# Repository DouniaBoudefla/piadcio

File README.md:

PIADC-IO

PIADC-IO is a versatile and I/O expansion project designed to enhance the GPIO capabilities of the Raspberry Pi. The project integrates the MCP23S08 I/O expander and the MCP3208 ADC (Analog-to-Digital Converter) with the Raspberry Pi, enabling efficient control of multiple devices and precise analog signal measurements via the SPI protocol. This repository contains all the necessary resources, including schematics, PCB designs, code, and documentation, to set up and use the PIADC-IO system for various applications, such as slow control in experimental setups and monitoring analog inputs.

Features

I/O Expansion: Utilize the MCP23S08 to expand the Raspberry Pi's GPIO capabilities by 8 configurable pins per expander, supporting multiple input/output configurations.
Analog-to-Digital Conversion: Integrate the MCP3208 to enable reading from up to 8 analog input channels with 12-bit resolution.
Power Indication LED: Monitor power status with a controllable LED, which can be managed via the Raspberry Pi.
Modular and Configurable: Easily adapt the system to different hardware setups with a TOML configuration file used to define hardware-specific settings like SPI bus numbers and chip select lines.

Repository Structure

pcb/ - Includes PCB design files and contains the electronic schematics used for the project, designed in KiCad.
src/ - Source code for interacting with the MCP23S08 and MCP3208, including Python classes for each.

Preliminary Configuration

Before starting, you need to enable the SPI function on your Raspberry Pi using 'raspi-config'.
The Raspberry Pi have 2 different SPI bus: one will be known as /dev/spi0.* and the other as /dev/spi1.*.

Enabling SPI1

if '/dev/spi1.0' and '/dev/spi1.1' are not available, you need to enable SPI1 manually:

1. Edit the boot configuration file:

        sudo nano /boot/config.txt

2. Add the following lines at the end of the file to enable SPI1:

        dtparam=spi=on
        dtoverlay=spi1-3cs

3. Save the file and exit the editor (Ctrl + O, Enter, Ctrl + X)
4. Reboot your Raspberry Pi to apply the changes:

        sudo reboot

After rebooting, you should see '/dev/spi1.0' and '/dev/spi1.1' available for use.

Communication with MCP23S08

To communicate with MCP23S08, you need to send and receive data via the SPI interface. Here is how you can read from and write to the the MCP23S08 registers using Python with the 'spidev' library.

Understanding MCP23S08 Communication

Commmand Structure

Communication with the MCP23S08 involves sending a sequence of bytes over the SPI interface. 
Each command generally consists of the following parts:

- Opcode: Determines whether the operation is a read or write
- Register Address: Specifies which register to access
- Data: The value to write to the register (for write operations)

Opcode

Write Opcode: Ox40 (A0=0, A1=0)
Read Opcode: 0x41 (A0=0, A1=0)

The opcode is followed by the register address and then the data byte

Register Address

The MCP23S08 has several registers for configuring and controlling the I/Os. Here are some key registers:

- IODIR (0X00): I/O Direction Register (1 = input, 0 = output)
- GPIO (0x09): GPIO Register (read/write I/O values)
- OLAT (0x0A): Output Latch Register (maintain output values)

Data 

The data byte is the value you write to the register. For read operations, the data byte received from the MCP23S08 will contain the registers's current value.

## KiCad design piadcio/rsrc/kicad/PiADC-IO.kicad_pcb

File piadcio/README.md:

PIADC-IO

PIADC-IO is a versatile and I/O expansion project designed to enhance the GPIO capabilities of the Raspberry Pi. The project integrates the MCP23S08 I/O expander and the MCP3208 ADC (Analog-to-Digital Converter) with the Raspberry Pi, enabling efficient control of multiple devices and precise analog signal measurements via the SPI protocol. This repository contains all the necessary resources, including schematics, PCB designs, code, and documentation, to set up and use the PIADC-IO system for various applications, such as slow control in experimental setups and monitoring analog inputs.

Features

I/O Expansion: Utilize the MCP23S08 to expand the Raspberry Pi's GPIO capabilities by 8 configurable pins per expander, supporting multiple input/output configurations.
Analog-to-Digital Conversion: Integrate the MCP3208 to enable reading from up to 8 analog input channels with 12-bit resolution.
Power Indication LED: Monitor power status with a controllable LED, which can be managed via the Raspberry Pi.
Modular and Configurable: Easily adapt the system to different hardware setups with a TOML configuration file used to define hardware-specific settings like SPI bus numbers and chip select lines.

Repository Structure

pcb/ - Includes PCB design files and contains the electronic schematics used for the project, designed in KiCad.
src/ - Source code for interacting with the MCP23S08 and MCP3208, including Python classes for each.

Preliminary Configuration

Before starting, you need to enable the SPI function on your Raspberry Pi using 'raspi-config'.
The Raspberry Pi have 2 different SPI bus: one will be known as /dev/spi0.* and the other as /dev/spi1.*.

Enabling SPI1

    if '/dev/spi1.0' and '/dev/spi1.1' are not available, you need to enable SPI1 manually:

    1. Edit the boot configuration file:

        sudo nano /boot/config.txt

    2. Add the following lines at the end of the file to enable SPI1:

        dtparam=spi=on
        dtoverlay=spi1-3cs

    3. Save the file and exit the editor (Ctrl + O, Enter, Ctrl + X)
    4. Reboot your Raspberry Pi to apply the changes:

        sudo reboot

    After rebooting, you should see '/dev/spi1.0' and '/dev/spi1.1' available for use.

Communication with MCP23S08

To communicate with MCP23S08, you need to send and receive data via the SPI interface. Here is how you can read from and write to the the MCP23S08 registers using Python with the 'spidev' library.

Understanding MCP23S08 Communication

Commmand Structure

Communication with the MCP23S08 involves sending a sequence of bytes over the SPI interface. 
Each command generally consists of the following parts:

- Opcode: Determines whether the operation is a read or write
- Register Address: Specifies which register to access
- Data: The value to write to the register (for write operations)

Opcode

Write Opcode: Ox40 (A0=0, A1=0)
Read Opcode: 0x41 (A0=0, A1=0)

The opcode is followed by the register address and then the data byte

Register Address

The MCP23S08 has several registers for configuring and controlling the I/Os. Here are some key registers:

- IODIR (0X00): I/O Direction Register (1 = input, 0 = output)
- GPIO (0x09): GPIO Register (read/write I/O values)
- OLAT (0x0A): Output Latch Register (maintain output values)

Data 

The data byte is the value you write to the register. For read operations, the data byte received from the MCP23S08 will contain the registers's current value.

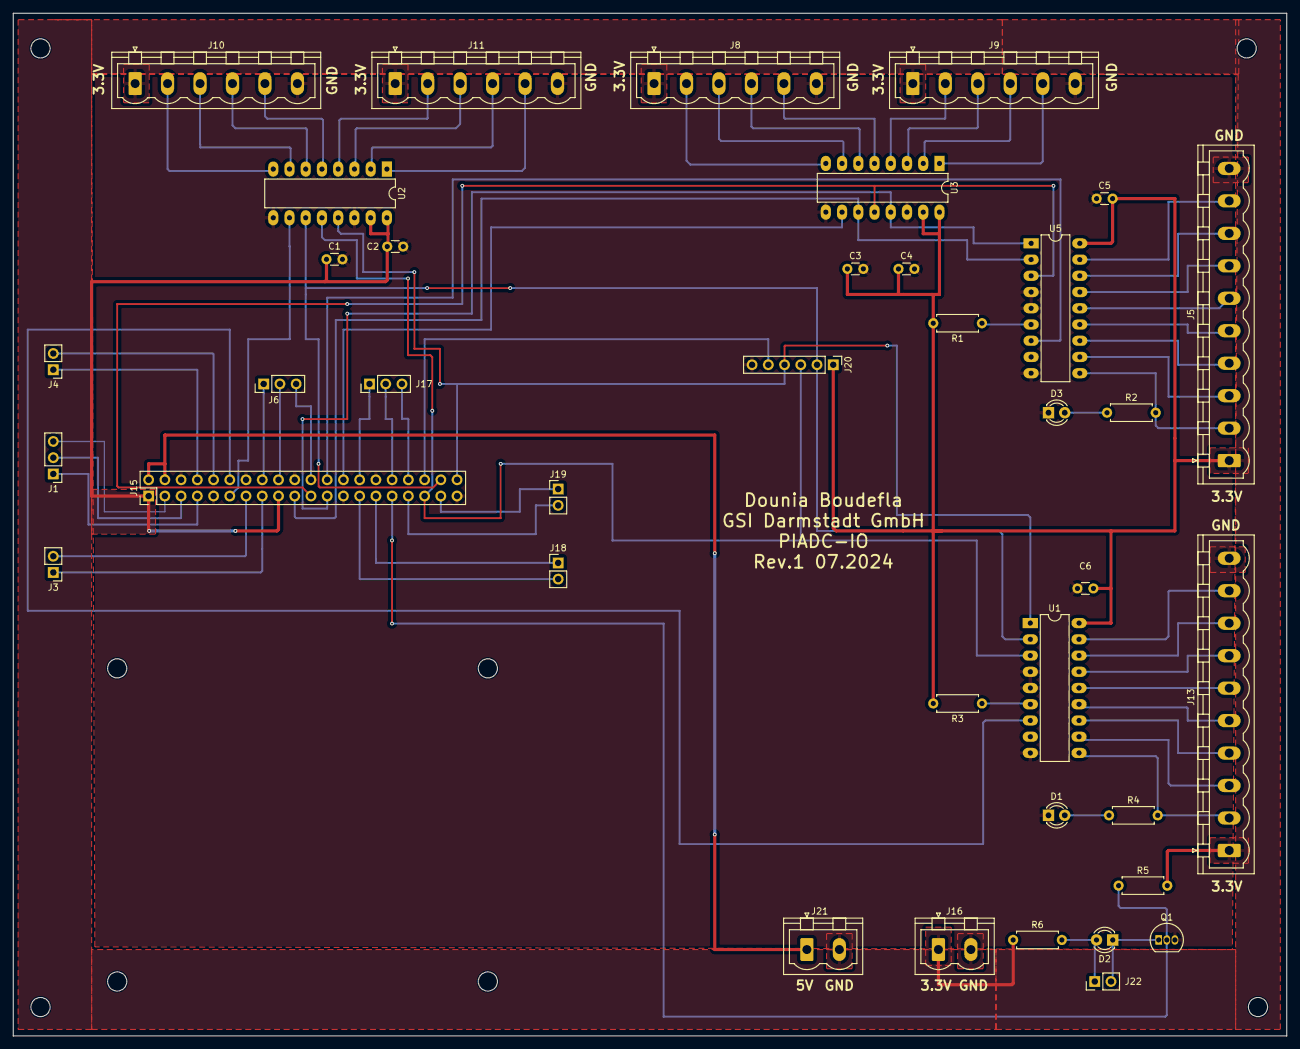
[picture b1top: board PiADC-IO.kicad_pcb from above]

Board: 2 copper layers, 199.3 x 160.0 mm, 43 parts (0 on the bottom side), 70 nets.

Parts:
C1, C3: 10nF; C_Disc_D3.0mm_W1.6mm_P2.50mm
C2, C4, C5, C6: 100nF; C_Disc_D3.0mm_W1.6mm_P2.50mm
D1, D2, D3: LED Red; LED_D3.0mm
H1, H2, H3, H4: MountingHole; MountingHole_3mm
J1, J6, J17: Conn_01x03; PinHeader_1x03_P2.54mm_Vertical
J2: Raspberry_Pi_2_3; raspberrypi_NOCONNECTOR
J3, J4, J18, J19, J22: Conn_01x02; PinHeader_1x02_P2.54mm_Vertical
J5, J13: Conn_01x10; PhoenixContact_MSTBVA_2,5_10-G-5,08_1x10_P5.08mm_Vertical
J8, J9, J10, J11: Conn_01x06; PhoenixContact_MSTBVA_2,5_6-G-5,08_1x06_P5.08mm_Vertical
J15: RPI conn; PinHeader_2x20_P2.54mm_Vertical
J16: Raspberry Pi USB Power; PhoenixContact_MSTBVA_2,5_2-G-5,08_1x02_P5.08mm_Vertical
J20: Conn_01x06; PinHeader_1x06_P2.54mm_Vertical
J21: 5V; PhoenixContact_MSTBVA_2,5_2-G-5,08_1x02_P5.08mm_Vertical
Q1: BS170; TO-92_Inline
R1, R3, R5: 4.7K; R_Axial_DIN0207_L6.3mm_D2.5mm_P7.62mm_Horizontal
R2, R4, R6: 470R; R_Axial_DIN0207_L6.3mm_D2.5mm_P7.62mm_Horizontal
U1, U5: MCP23S08-I/O Expander; DIP-18_W7.62mm_LongPads
U2, U3: MCP3208-ADC; DIP-16_W7.62mm_LongPads

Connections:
+3.3V: C1.1, C2.1, C3.1, C4.1, C5.2, C6.2, J5.1, J8.1, J9.1, J10.1, J11.1, J13.1, J15.1, J15.17, J16.1, J20.1, R1.2, R3.2, R5.2, R6.1, U1.18 (VDD), U2.15 (Vref), U2.16 (Vdd), U3.15 (Vref), U3.16 (Vdd), U5.18 (VDD)
+5V: J15.2, J15.4, J21.1
/CS 0_0: J15.24, U5.7 (~CS)
/CS 0_1: J15.26, U3.10 (~CS/SHDN)
/CS 1_0: J15.12, U1.7 (~CS)
/CS 1_1: J15.11, U2.10 (~CS/SHDN)
/CS 1_2: J15.36, J20.5
/MISO 0: J15.21, U3.12 (Dout), U5.3 (SO)
/MISO 1: J15.35, J20.3, U1.3 (SO), U2.12 (Dout)
/MOSI 0: J15.19, U3.11 (Din), U5.2 (SI)
/MOSI 1: J15.38, J20.2, U1.2 (SI), U2.11 (Din)
/SCLK 0: J15.23, U3.13 (CLK), U5.1 (SCK)
/SCLK 1: J15.40, J20.4, U1.1 (SCK), U2.13 (CLK)
GND: C1.2, C2.2, C3.2, C4.2, C5.1, C6.1, D1.1 (K), D3.1 (K), J5.10, J8.6, J9.6, J10.6, J11.6, J13.10, J15.6, J15.9, J15.14, J15.20, J15.25, J15.30, J15.39, J16.2, J20.6, J21.2, Q1.3 (S), U1.4 (A1), U1.5 (A0), U1.9 (VSS), U2.9 (DGND), U2.14 (AGND), U3.9 (DGND), U3.14 (AGND), U5.4 (A1), U5.5 (A0), U5.9 (VSS)
unnamed: D1.2 (A), R4.1
unnamed: D2.2 (A), J22.1, R6.2
unnamed: D2.1 (K), J22.2, Q1.1 (D)
unnamed: D3.2 (A), R2.1
unnamed: J1.1, J15.7
unnamed: J1.2, J15.5
unnamed: J1.3, J15.3
unnamed: J5.2, R2.2, U5.10 (GP0)
unnamed: J5.3, U5.11 (GP1)
unnamed: J5.4, U5.12 (GP2)
unnamed: J5.5, U5.13 (GP3)
unnamed: J5.6, U5.14 (GP4)
unnamed: J5.7, U5.15 (GP5)
unnamed: J5.8, U5.16 (GP6)
unnamed: J5.9, U5.17 (GP7)
unnamed: J8.2, U3.8 (CH7)
unnamed: J8.3, U3.7 (CH6)
unnamed: J8.4, U3.6 (CH5)
unnamed: J8.5, U3.5 (CH4)
unnamed: J9.2, U3.4 (CH3)
unnamed: J9.3, U3.3 (CH2)
unnamed: J9.4, U3.2 (CH1)
unnamed: J9.5, U3.1 (CH0)
unnamed: J10.2, U2.8 (CH7)
unnamed: J10.3, U2.7 (CH6)
unnamed: J10.4, U2.6 (CH5)
unnamed: J10.5, U2.5 (CH4)
unnamed: J11.2, U2.4 (CH3)
unnamed: J11.3, U2.3 (CH2)
unnamed: J11.4, U2.2 (CH1)
unnamed: J11.5, U2.1 (CH0)
unnamed: J13.2, R4.2, U1.10 (GP0)
unnamed: J13.3, U1.11 (GP1)
unnamed: J13.4, U1.12 (GP2)
unnamed: J13.5, U1.13 (GP3)
unnamed: J13.6, U1.14 (GP4)
unnamed: J13.7, U1.15 (GP5)
unnamed: J13.8, U1.16 (GP6)
unnamed: J13.9, U1.17 (GP7)
unnamed: J4.1, J15.8
unnamed: J4.2, J15.10
unnamed: J3.2, J15.13
unnamed: J3.1, J15.15
unnamed: J6.1, J15.16
unnamed: J6.2, J15.18
unnamed: J6.3, J15.22
unnamed: J15.27, J18.2
unnamed: J15.28, J17.1
unnamed: J15.29, J18.1
unnamed: J15.31, Q1.2 (G), R5.1
unnamed: J15.32, J17.2
unnamed: J15.33, J19.2
unnamed: J15.34, J17.3
unnamed: J15.37, J19.1
unnamed: R3.1, U1.6 (~RESET)
unnamed: R1.1, U5.6 (~RESET)
